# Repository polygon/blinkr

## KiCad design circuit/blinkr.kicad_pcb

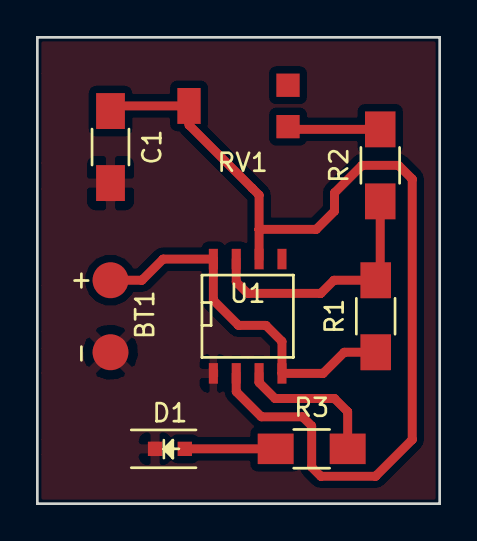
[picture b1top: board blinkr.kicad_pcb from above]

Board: 2 copper layers, 22.4 x 25.9 mm, 8 parts (0 on the bottom side), 7 nets.

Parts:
BT1: Battery; battery_connect
C1: 10µ; C_1206_HandSoldering
D1: LED; LED_1608
R1: 1k; R_1206_HandSoldering
R2: 10k; R_1206_HandSoldering
R3: 200; R_1206_HandSoldering
RV1: 250k; Bourne-3314G-1
U1: NE555D; SOIC-8-N

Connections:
GND: BT1.2, C1.2, D1.1, U1.1
unnamed: C1.1, RV1.2, U1.2, U1.6
unnamed: D1.2, R3.1
unnamed: R1.2, R2.1, U1.7
unnamed: R2.2, RV1.1
unnamed: R3.2, U1.3
VCC: BT1.1, R1.1, U1.4, U1.8

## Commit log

2017-06-24 Blinkr circuit
2017-07-02 Copper layer SVG export
2017-07-02 Schematic and board with prints SVG exports
2017-07-05 Step1
2017-07-05 Step2-4
2017-07-05 Presentation
